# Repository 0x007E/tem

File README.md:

# `TEM` - TWI EEPROM Module

The `TEM` is a board with an [AT24CM0X](#additional-information) `EEPROM` or any other `EEPROM` that fits the pin setting of the board. The board itself is driven with a voltage from `3V3`-`5V`. The `EEPROM` can be protected from being written with the onboard switch `SW1`.

> The address setup of the `EEPROMs` can be setup with Jumper `JP1`/`JP2`for the first `EEPROM` and Jumper `JP3`/`JP4` for the second `EEPROM`.

| Experience | Level |
|:------------|:-----:|
| Soldering   |  |
| Mechanical    |  |

# Downloads

| Type      | File               | Description              |
|:---------:|:------------------:|:-------------------------|
| Schematic | [pdf](https://github.com/0x007E/tem/releases/latest/download/schematic.pdf) / [cadlab](https://cadlab.io/project/29791/main/files) | Schematic files |
| Board | [pdf](https://github.com/0x007E/tem/releases/latest/download/pcb.pdf) / [cadlab](https://cadlab.io/project/29791/main/files) | Board file |
| Drill | [pdf](https://github.com/0x007E/tem/releases/latest/download/drill.pdf) | Drill file |
| PCB | [zip](https://github.com/0x007E/tem/releases/latest/download/kicad.zip) / [tar](https://github.com/0x007E/tem/releases/latest/download/kicad.tar.gz) |  	KiCAD/Gerber/BoM/Drill files |
| Mechanical | [zip](https://github.com/0x007E/diu/releases/latest/download/freecad.zip) / [tar](https://github.com/0x007E/diu/releases/latest/download/freecad.tar.gz) | FreeCAD/Housing and PCB (STEP) files     |

# Hardware

The pcb is created with `KiCAD`, the housing with `FreeCAD`. All files are built with `github actions` so that they are ready for a production environment.

## PCB

The circuit board is populated on both sides (Top, Bottom). The best way for soldering the `SMD` components is within a vapor phase soldering system and for the `THT` components with a standard soldering system.

### Top Layer

### Bottom Layer

## Mechanical

The housing has a tolerance of `0.2mm` on each side of the case. So the pcb should fit perfectly in the housing. The tolerance can be modified with `FreeCAD` in the `Parameter` Spreadsheet.

### Assembled

### Exploded

# Additional Information

| Type       | Link               | Description              |
|:----------:|:------------------:|:-------------------------|
| AT24CM02 | [pdf](https://ww1.microchip.com/downloads/en/DeviceDoc/AT24CM02-I2C-Compatible-Two-Wire-Serial-EEPROM-2-Mbit-262,144x8-20006197C.pdf) | 2-MBit serial EEPROM dataseheet |
| AT24CM01 | [pdf](https://ww1.microchip.com/downloads/en/DeviceDoc/AT24CM01-I2C-Compatible-Two-Wire-Serial-EEPROM-Data-Sheet-20006170A.pdf) | 1-MBit serial EEPROM datasheet |

---

R. GAECHTER

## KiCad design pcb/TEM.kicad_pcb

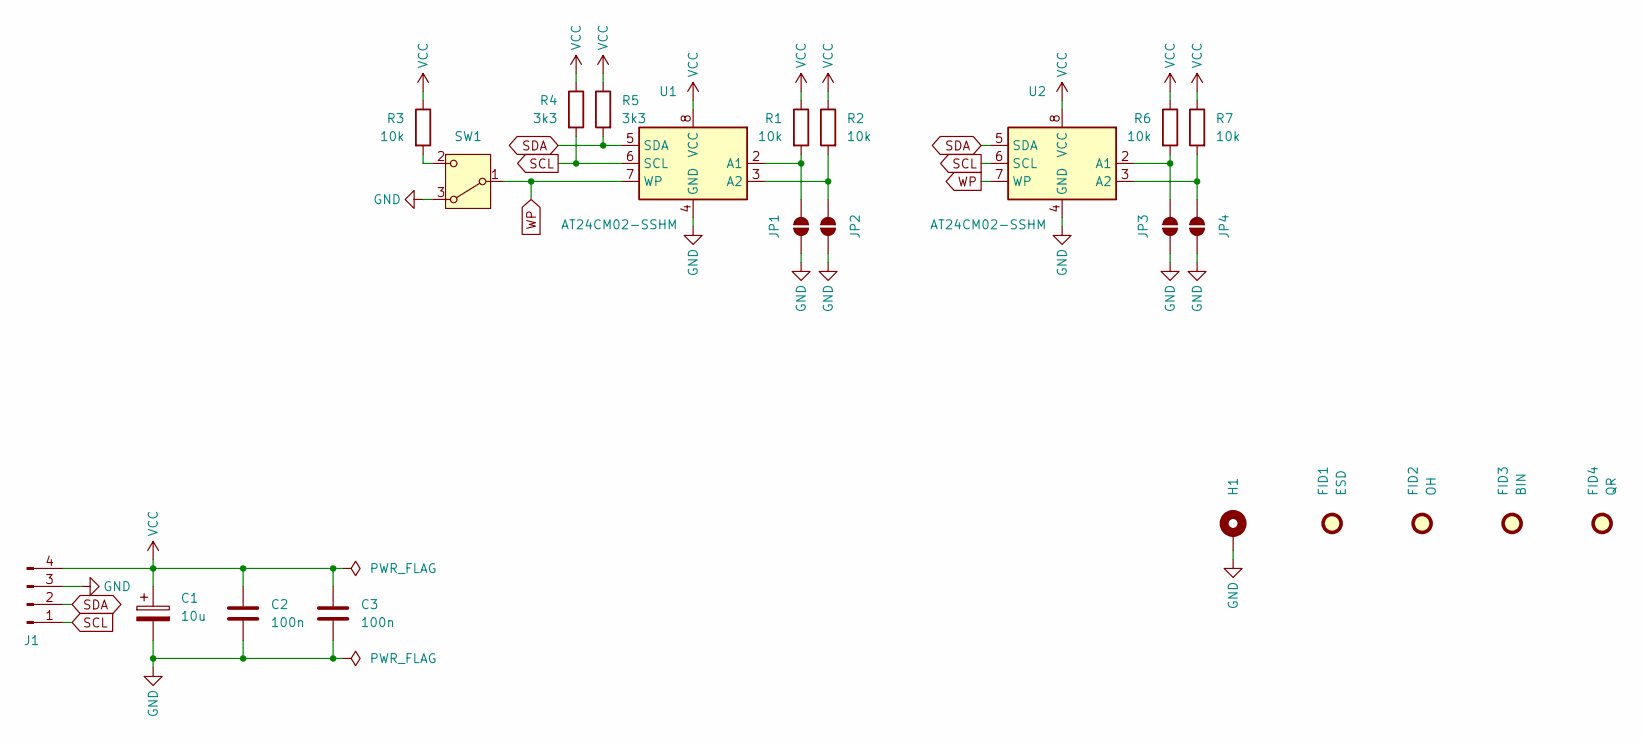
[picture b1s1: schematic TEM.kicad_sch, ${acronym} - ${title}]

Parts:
C1: 10u; CP_EIA-6032-28_Kemet-C
C2, C3: 100n; C_1206_3216Metric
FID1: ESD; ESD-Logo_6.6x6mm_SilkScreen
FID2: OH; OSHW-Logo_5.7x6mm_SilkScreen
FID3: BIN; WEEE-Logo_4.2x6mm_SilkScreen
FID4: QR; QR_0x007e_very_small
H1: MountingHole_Pad; MountingHole_2.7mm_M2.5_DIN965_Pad
J1: Conn_01x04_Pin; PinHeader_1x04_P2.54mm_Horizontal
JP1, JP2, JP3, JP4: SolderJumper_2_Open; SolderJumper-2_P1.3mm_Open_RoundedPad1.0x1.5mm
R1, R2, R3, R6, R7: 10k; R_1206_3216Metric
R4, R5: 3k3; R_1206_3216Metric
SW1: SW_Wuerth_450301014042; SW_Slide-03_Wuerth-WS-SLTV_10x2.5x6.4_P2.54mm
U1, U2: AT24CM02-SSHM; SOIC-8_3.9x4.9mm_P1.27mm

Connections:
GND: C1.2, C2.2, C3.2, H1.1, J1.3, JP1.1 (A), JP2.1 (A), JP3.1 (A), JP4.1 (A), SW1.3 (A), U1.4 (GND), U2.4 (GND)
unnamed: JP1.2 (B), R1.2, U1.2 (A1)
unnamed: JP2.2 (B), R2.2, U1.3 (A2)
unnamed: JP3.2 (B), R6.2, U2.2 (A1)
unnamed: JP4.2 (B), R7.2, U2.3 (A2)
unnamed: R3.2, SW1.2 (C)
SCL: J1.1, R4.2, U1.6 (SCL), U2.6 (SCL)
SDA: J1.2, R5.2, U1.5 (SDA), U2.5 (SDA)
VCC: C1.1, C2.1, C3.1, J1.4, R1.1, R2.1, R3.1, R4.1, R5.1, R6.1, R7.1, U1.8 (VCC), U2.8 (VCC)
WP: SW1.1 (B), U1.7 (WP), U2.7 (WP)

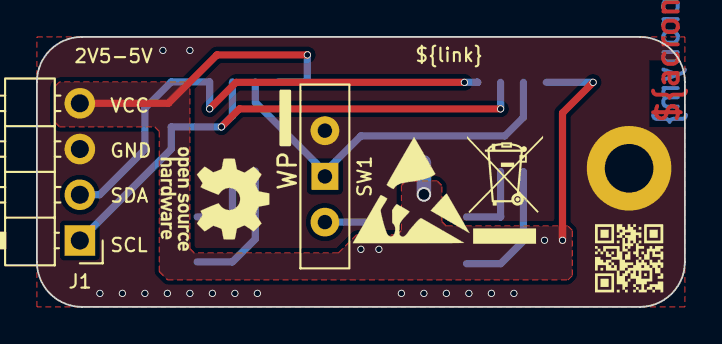
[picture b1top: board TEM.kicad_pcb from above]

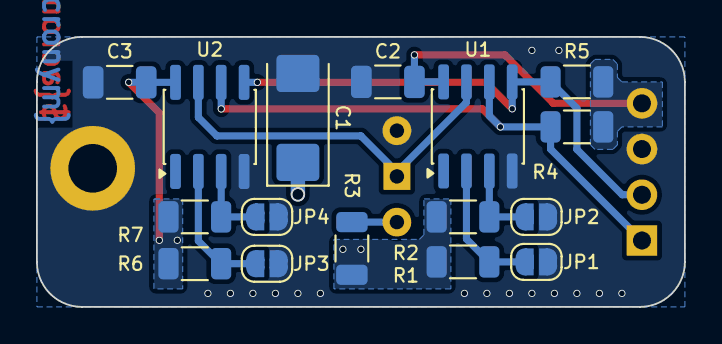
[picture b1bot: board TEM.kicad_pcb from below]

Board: 2 copper layers, 36.0 x 15.0 mm, 23 parts (16 on the bottom side), 10 nets.

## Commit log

2025-12-10 Add pcb layout
2025-12-10 Add mechanical parts
2025-12-10 Swapped SCL/SDA
2025-12-10 Adapt vendors on partlist
2026-01-08 Exclude json
2026-01-08 Add vendor id to partlist
2026-02-05 Add assembly explosion
2026-02-05 Add images to .gitignore
2026-02-05 Add README.md
2026-02-05 Add build pipeline
2026-02-05 Add release pipeline
2026-02-05 Fix README.md title
2026-02-06 Add mechanical part
2026-02-06 Switched system language
2026-03-09 Remove invalid text
2026-03-09 Update footprints
2026-03-16 Replace WP on silkscreen
2026-03-16 Replace WP on acrylglass
2026-04-08 Remove exclude from bom
2026-04-08 Add missing vendor(id)
2026-04-22 Adapt vendor(id)

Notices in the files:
README.md:
License CC By-NC-SA
parts and their libraries:
license: CC BY-NC-SA 4.0
